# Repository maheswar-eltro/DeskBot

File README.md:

# DeskBot — ESP32-C3 Interactive Desktop Companion

An interactive embedded desktop companion built around the ESP32-C3 Super Mini, combining animated OLED expressions, digital audio processing, motion sensing, real-time visualisation and physics simulation.

DeskBot explores the intersection of embedded systems, digital signal processing, sensor integration, real-time graphics and human–robot interaction.

Rather than functioning as a conventional robotic vehicle, DeskBot incorporates multiple interactive experiences into a compact embedded platform.

---

## Project Gallery

### Working Breadboard Prototype

The initial DeskBot prototype, integrating the ESP32-C3, OLED display, digital audio hardware and speaker on a breadboard.

### Early Hardware Exploration

Initial component exploration during the development of DeskBot. Some components shown here were part of earlier experiments and are not included in the current hardware configuration.

---

## Features

### 1. Interactive OLED Companion

- Animated facial expressions using a 0.96-inch SSD1306 OLED.
- Sound-triggered reactions.
- Clap detection and double-clap interaction.
- Motion-responsive behaviour using the MPU6050.
- Inactivity-based sleepy state and wake-up responses.

### 2. Real-Time Audio Spectrum Analyzer

- Live audio acquisition through the INMP441 microphone.
- Custom radix-2 Cooley-Tukey FFT implementation.
- Mean removal and Hann windowing.
- 16-band frequency visualisation.
- Dynamic spectrum bars and peak-hold indicators.

### 3. Optical Illusion Engine

Three monochrome visual experiments:

- **Rubin's Vase:** Figure-ground perception illusion.
- **Hypnotic Tunnel:** Animated concentric-circle visualisation.
- **Hermann Grid:** Grid-based optical illusion.

### 4. Tilt-Controlled Physics Simulator

- 40-particle simulation.
- MPU6050-based tilt interaction.
- Velocity-based particle movement.
- Boundary and particle collision handling.
- Damping and particle-scattering interaction.

### 5. Voice Mimic

Two independent implementations exploring audio recording and playback:

| Implementation | Recording Duration | PCM Format | Sampling Rate |
|---|---:|---|---:|
| 5-second version | 5 seconds | 16-bit mono | 16 kHz |
| 10-second version | 10 seconds | 8-bit mono | 16 kHz |

Both implementations use the INMP441 microphone and MAX98357A audio amplifier.

---

## Hardware

The ESP32-C3 Super Mini acts as the central controller.

| Component | Function |
|---|---|
| ESP32-C3 Super Mini | Main controller |
| SSD1306 OLED, 128×64 | Visual output and animations |
| MPU6050 | Accelerometer and gyroscope |
| INMP441 | Digital MEMS microphone |
| MAX98357A | I2S audio amplifier |
| 4Ω speaker | Audio output |
| 2 × Push Buttons | Physical user interaction |

### Communication Interfaces

| Interface | Connected Hardware | Purpose |
|---|---|---|
| I2C | OLED, MPU6050 | Display and sensor communication |
| I2S | INMP441, MAX98357A | Digital audio input and output |
| GPIO | Push buttons | User input |

### Power

The working breadboard prototype uses a USB power bank connected to the ESP32-C3 through USB-C.

The hardware design uses 5V and 3.3V power rails with a common ground reference.

---

## System Architecture

The ESP32-C3 coordinates the different hardware peripherals and application functions.

```text
                    ESP32-C3
                        |
        +---------------+---------------+
        |               |               |
       I2C             I2S             GPIO
        |               |               |
   +----+----+     +----+----+      Push Buttons
   |         |     |         |
  OLED    MPU6050 INMP441  MAX98357A
                              |
                           Speaker
```

### Operating Modes

DeskBot combines four primary operating modes:

1. **Interactive Companion** — Animated expressions and sound/motion-based reactions.
2. **Audio Spectrum Analyzer** — Real-time frequency-domain visualisation.
3. **Optical Illusion Engine** — Three monochrome visual experiments.
4. **Physics Simulator** — Tilt-controlled particle simulation.

The integrated firmware also includes voice-mimic functionality.

For a detailed explanation, see [System Architecture](documentation/system-architecture.md).

---

## Custom PCB Design

A dedicated two-layer PCB was designed using KiCad to consolidate the hardware connections.

### Circuit Schematic

The complete circuit schematic illustrates the electrical connections between the ESP32-C3 and the connected peripherals.

### PCB Layout

The following views show the top and bottom PCB layouts.

| Top Layer | Bottom Layer |
|:---:|:---:|
|  |  |

### 3D PCB Model

3D renders provide a visual representation of the board and its component arrangement.

| Front View | Back View | Side View |
|:---:|:---:|:---:|
|  |  |  |

### PCB Specifications

| Parameter | Specification |
|---|---|
| Design software | KiCad 10 |
| Board dimensions | 74.55 × 60.55 mm |
| Copper layers | 2 |
| Board thickness | 1.6 mm |
| Substrate | FR4 |
| Grounding | GND copper zones on both layers |

The PCB provides dedicated connections for the ESP32-C3, OLED, microphone, amplifier, MPU6050 and push buttons.

### Design Verification

The initial KiCad Design Rule Check reported:

- 0 PCB violations.
- 0 unconnected items.
- 1 extra-footprint schematic-parity warning associated with the PCB logo.
- 5 ignored tests.

The PCB design and manufacturing files have been prepared. Physical fabrication, assembly and validation remain pending.

**PCB Resources:**

- [Editable KiCad Project](hardware/pcb/kicad/)
- [Gerber Manufacturing Files](hardware/pcb/gerbers/)
- [PCB Documentation](hardware/pcb/README.md)
- [Detailed PCB Design Notes](documentation/pcb-design.md)

---

## Repository Structure

```text
DeskBot/
│
├── README.md
│
├── assets/
│   └── images/
│       ├── prototype/
│       │   ├── deskbot-prototype.jpg
│       │   └── deskbot-prototype2.jpg
│       │
│       ├── features/
│       │   ├── audio-spectrum.gif
│       │   ├── audio-spectrum.jpg
│       │   ├── companion-display.gif
│       │   ├── companion-display.jpg
│       │   ├── particle-simulator.gif
│       │   ├── particle-simulator.jpg
│       │   ├── visual-experiment.gif
│       │   └── visual-experiment.jpg
│       │
│       ├── pcb/
│       │   ├── schematic.png
│       │   ├── pcb-top.png
│       │   ├── pcb-bottom.png
│       │   ├── pcb-3d-front.png
│       │   └── pcb-3d-back.png
│       │   └── pcb-3d-tilted.png
│       │
│       └── early-hardware-components.jpeg
│
├── documentation/
│   ├── design.md
│   ├── notes.md
│   ├── pcb-design.md
│   ├── progress.md
│   └── system-architecture.md
│
├── hardware/
│   ├── components.md
│   ├── pinout.md
│   ├── wiring.md
│   │
│   └── pcb/
│       ├── README.md
│       ├── gerbers/
│       └── kicad/
│           ├── pilot.kicad_pcb
│           ├── pilot.kicad_pro
│           └── pilot.kicad_sch
│
└── src/
    ├── main/
    │   └── bot/
    │       ├── eyes/
    │       ├── mimic/
    │       │   ├── 5secs/
    │       │   └── 10secs/
    │       └── proto/
    │
    └── tests/
        ├── audio/
        │   ├── MAX98/
        │   └── mic/
        │
        ├── display/
        │   └── OLED/
        │
        └── sensors/
            └── mpu6050/
```

### Directory Guide

| Directory | Purpose |
|---|---|
| `assets/images/` | Prototype photographs, feature demonstrations and PCB previews |
| `documentation/` | Design decisions, engineering notes, architecture and progress |
| `hardware/` | Component inventory, pinout, wiring and PCB resources |
| `hardware/pcb/kicad/` | Editable KiCad project files |
| `hardware/pcb/gerbers/` | PCB manufacturing outputs |
| `src/main/bot/` | Main firmware and integrated prototype |
| `src/main/bot/mimic/` | Independent voice-mimic implementations |
| `src/tests/` | Standalone hardware experiments and peripheral tests |

---

## Getting Started

### Requirements

- Arduino IDE or compatible development environment.
- ESP32 board support package.
- ESP32-C3 Super Mini.
- USB-C data cable.
- Required peripheral libraries used by the firmware.

### Running the Firmware

1. Clone or download the repository.
2. Install the ESP32 board support package.
3. Connect the ESP32-C3 using a USB-C data cable.
4. Select the appropriate ESP32-C3 board configuration and serial port.
5. Open the desired `.ino` file from the source directory.
6. Install any required libraries referenced by that sketch.
7. Compile and upload the firmware.

### Main Firmware

The integrated prototype is located at:

`src/main/bot/proto/proto.ino`

### Voice Mimic Implementations

The independent implementations are located at:

- `src/main/bot/mimic/5secs/5secs.ino`
- `src/main/bot/mimic/10secs/10secs.ino`

The standalone test sketches can be found under `src/tests/`.

**Note:** The integrated prototype and individual test sketches are separate firmware programs. Upload the sketch corresponding to the functionality you want to test.

---

## Documentation

| Document | Description |
|---|---|
| [design.md](documentation/design.md) | Design philosophy, objectives and engineering decisions |
| [notes.md](documentation/notes.md) | Technical concepts and development learnings |
| [progress.md](documentation/progress.md) | Development milestones and project status |
| [system-architecture.md](documentation/system-architecture.md) | Firmware architecture and operating modes |
| [pcb-design.md](documentation/pcb-design.md) | Custom PCB design and verification |
| [components.md](hardware/components.md) | Hardware component inventory |
| [pinout.md](hardware/pinout.md) | ESP32-C3 and peripheral pin assignments |
| [wiring.md](hardware/wiring.md) | Electrical connections and communication interfaces |

---

## Development Status

| Subsystem | Status |
|---|---|
| OLED companion | Implemented and prototype-tested |
| Audio spectrum analyser | Implemented |
| Optical illusion engine | Implemented |
| Physics simulator | Implemented |
| Voice mimic | Two independent implementations |
| Integrated firmware | Working prototype |
| Custom PCB | Designed |
| PCB fabrication | Pending |
| PCB assembly and validation | Pending |

---

## Engineering Areas Explored

DeskBot provides practical experience in:

- Embedded C/C++ programming.
- ESP32-C3 development.
- I2C and I2S communication.
- Digital audio acquisition and playback.
- Digital signal processing and FFT.
- Sensor integration and motion detection.
- Real-time graphics and OLED animation.
- Mathematical physics simulation.
- Memory management in resource-constrained systems.
- PCB schematic capture and layout using KiCad.

---

## Project Goal

The objective of DeskBot is to develop a compact interactive embedded companion that brings together audio processing, motion sensing, visualisation and expressive behaviour.

The project demonstrates how independently developed hardware and software subsystems can be integrated into a unified embedded platform.

**DeskBot is an ongoing engineering project**, with further work focused on PCB fabrication, physical assembly, system validation and firmware improvements.

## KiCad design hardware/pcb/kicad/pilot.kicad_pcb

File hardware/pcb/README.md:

# DeskBot — PCB Resources

This directory contains the editable KiCad project and manufacturing exports for the custom DeskBot PCB.

## Directory Structure

```text
pcb/
│
├── README.md
│
├── kicad/
│   ├── pilot.kicad_pro
│   ├── pilot.kicad_sch
│   └── pilot.kicad_pcb
│
└── gerbers/
    └── Manufacturing files
```

## 1. KiCad Project

The `kicad/` directory contains the editable PCB design files.

| File | Description |
|---|---|
| `pilot.kicad_pro` | KiCad project configuration |
| `pilot.kicad_sch` | Electrical schematic |
| `pilot.kicad_pcb` | PCB layout, footprints and routing |

These files can be opened using KiCad for further schematic modifications and PCB layout development.

## 2. Gerber and Drill Files

The `gerbers/` directory contains the exported manufacturing files.

The package includes:

- Front and back copper layers.
- Front and back solder-mask layers.
- Front and back silkscreen layers.
- Board outline.
- Plated through-hole drill data.
- Non-plated through-hole drill data.
- Gerber job information.

These files describe the PCB layers and drilling information required by a PCB manufacturer.

## 3. PCB Specifications

| Parameter | Specification |
|---|---|
| Design software | KiCad 10 |
| Board dimensions | 74.55 × 60.55 mm |
| Copper layers | 2 |
| Board thickness | 1.6 mm |
| Substrate | FR4 |

## 4. Design Status

The schematic and PCB layout have been developed, and manufacturing exports have been generated.

Initial KiCad DRC results:

- 0 PCB violations.
- 0 unconnected items.
- 1 extra-footprint schematic-parity warning.

PCB fabrication, physical assembly and hardware validation are pending.

For the complete design explanation, refer to [`../../documentation/pcb-design.md`](../../documentation/pcb-design.md).

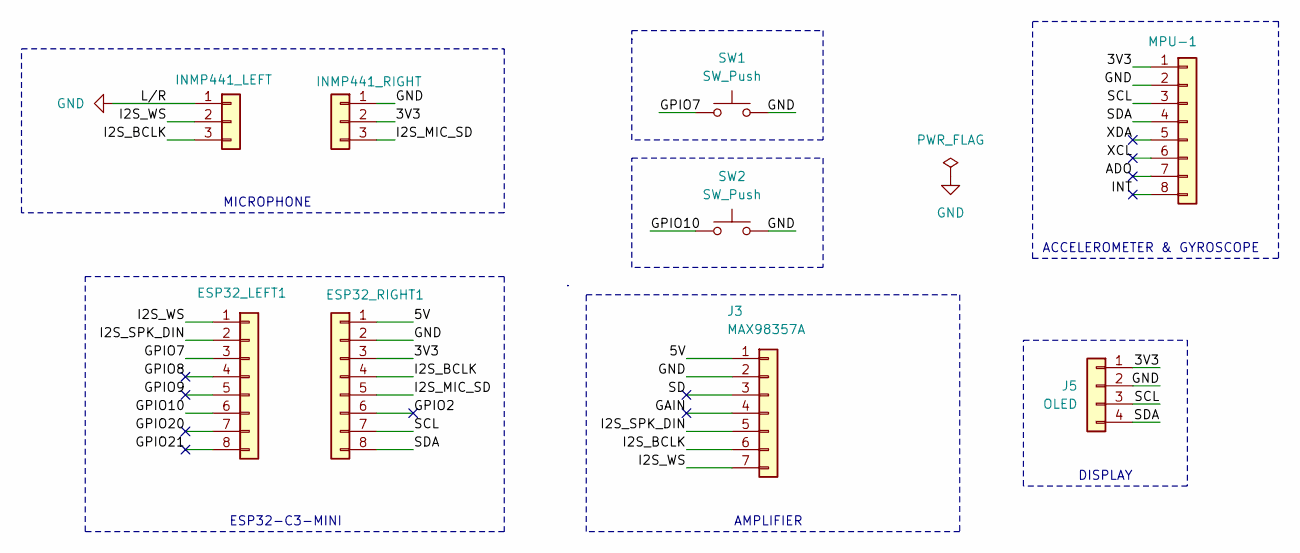
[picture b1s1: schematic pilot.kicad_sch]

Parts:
ESP32_LEFT1, ESP32_RIGHT1: Conn_01x08; PinSocket_1x08_P2.54mm_Vertical
J1: INMP441_LEFT; PinSocket_1x03_P2.54mm_Vertical
J2: INMP441_RIGHT; PinSocket_1x03_P2.54mm_Vertical
J3: MAX98357A; PinSocket_1x07_P2.54mm_Vertical
J5: OLED; PinSocket_1x04_P2.54mm_Vertical
MPU-1: MPU-6050; PinSocket_1x08_P2.54mm_Vertical
SW1, SW2: SW_Push; SW_PUSH_6mm

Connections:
/3V3: ESP32_RIGHT1.3, J2.2, J5.1, MPU-1.1
/5V: ESP32_RIGHT1.1, J3.1
/ADO: MPU-1.7
/GAIN: J3.4
/GPIO2: ESP32_RIGHT1.6
/GPIO7: ESP32_LEFT1.3, SW1.1
/GPIO8: ESP32_LEFT1.4
/GPIO9: ESP32_LEFT1.5
/GPIO10: ESP32_LEFT1.6, SW2.1
/GPIO20: ESP32_LEFT1.7
/GPIO21: ESP32_LEFT1.8
/I2S_BCLK: ESP32_RIGHT1.4, J1.3, J3.6
/I2S_MIC_SD: ESP32_RIGHT1.5, J2.3
/I2S_SPK_DIN: ESP32_LEFT1.2, J3.5
/I2S_WS: ESP32_LEFT1.1, J1.2, J3.7
/INT: MPU-1.8
/SCL: ESP32_RIGHT1.7, J5.3, MPU-1.3
/SD: J3.3
/SDA: ESP32_RIGHT1.8, J5.4, MPU-1.4
/XCL: MPU-1.6
/XDA: MPU-1.5
GND: ESP32_RIGHT1.2, J1.1, J2.1, J3.2, J5.2, MPU-1.2, SW1.2, SW2.2

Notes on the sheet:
ESP32-C3-MINI
ACCELEROMETER & GYROSCOPE
AMPLIFIER
MICROPHONE
DISPLAY

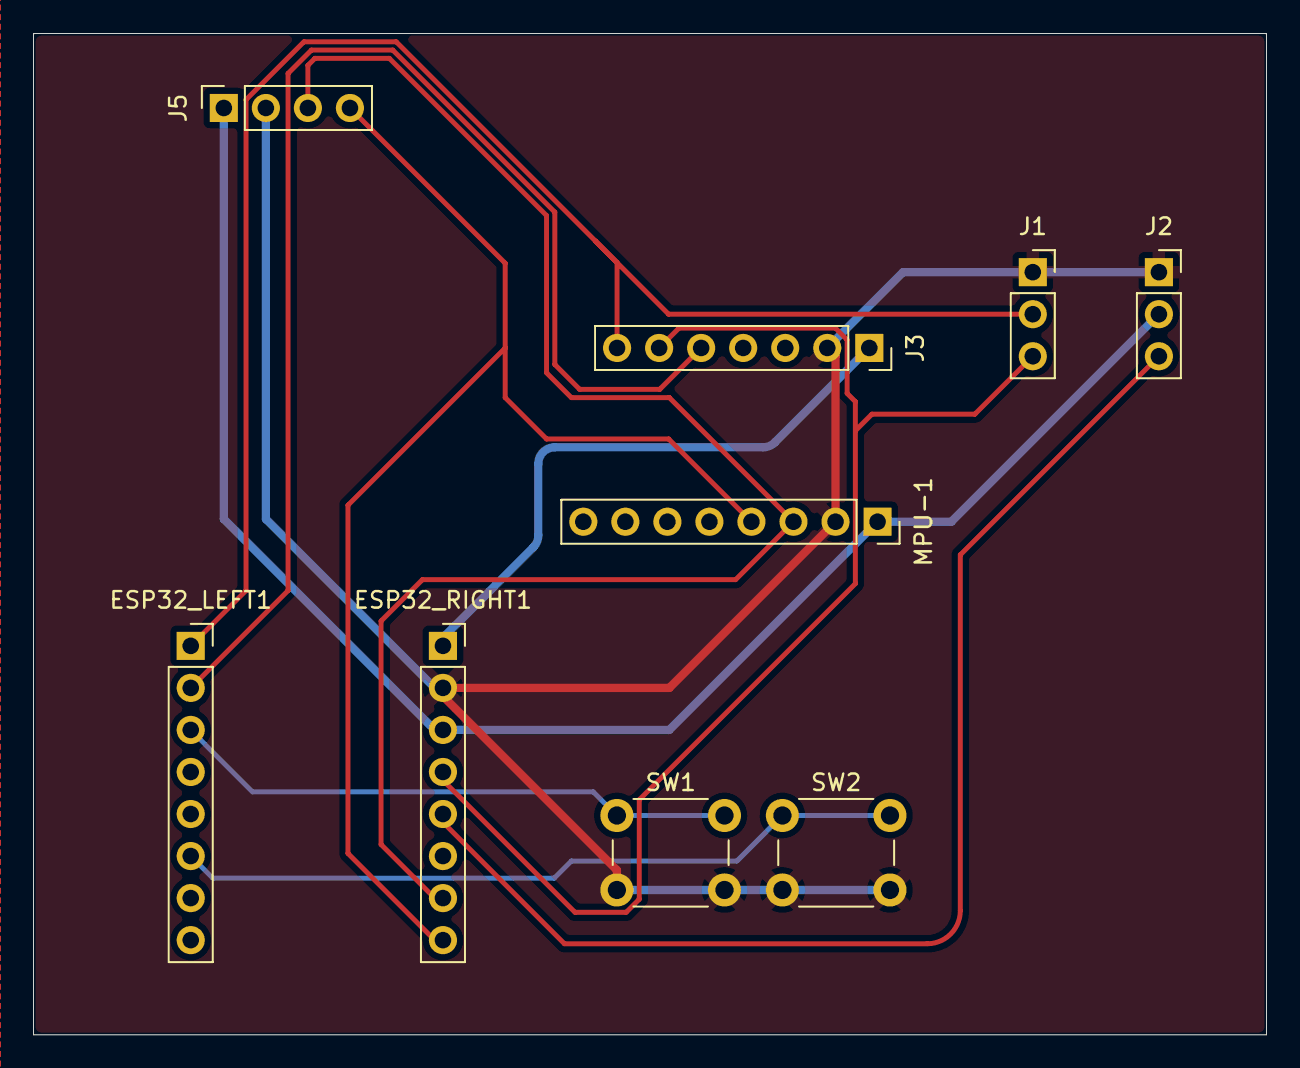
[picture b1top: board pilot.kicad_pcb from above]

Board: 2 copper layers, 74.5 x 60.5 mm, 9 parts (0 on the bottom side), 11 nets.
